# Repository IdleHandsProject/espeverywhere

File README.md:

# ESPEverywhere
ESP8266 Special Make/100 Kickstarter Edition

Check out why this board exists here:
https://www.youtube.com/watch?v=67Kh_ikb-ds

Thanks to the Backers of the #Make100(And the others as well!):  
Rolandas Launikonis  
Erlend Schei  
Andrew Chalkley  
Anthony Castaneda  
APSoft  
Arjuna Chatrathi  
Ashutosh Dubey  
Avinash Magdum  
BLUNT  
Bobby C C Wong  
Brian Linaburg  
Brian Willis  
Bruce Shipman  
Burrish  
DeltaLima  
Cardel Quaiatto  
Chaz Stone  
Chris Arnesen  
Christian Wilhelm  
Craig Hissett  
Dan Rothstein  
Danny Yo  
David Choi  
Death by snu snu  
Doug  
Fabio Cevasco  
Francisco Ribeiro  
Francesco Farruggia  
Grégoire Gustin  
Hank Terwilliger  
Hanya-zou  
Jeff Herndon  
Joe Key  
Jon Peer  
Jordan Moore  
Chris Cunningham  
Lewis Harrison-Wood  
Marco Hegenberg  
Mark Lee  
Mark Selph  
Milan Maletic  
Michael Gwincinski  
Mike Paulson  
Tim Lawson  
Michael Miranda  
Nick Piper  
Nick Goodall  
Nuno Santos  
PHK  
Wayne San  
Rob Arao  
Russell Calbert  
S. Lee Fowler  
Shabaz Mohammad  
SmilingRex Reyes  
Stephan Thomas  
Steve Farrage  
Will Ryan  
Yitzi Baum  

The ESP Everywhere was made to take part in the Kickstarter Make/100 Campaign
You can get 1 of 100 boards assembled by me. Or you can Make your own.
Kickstarter is here:
https://www.kickstarter.com/projects/idlehandsdev/esp-everywhere-kickstarter-special-make-100

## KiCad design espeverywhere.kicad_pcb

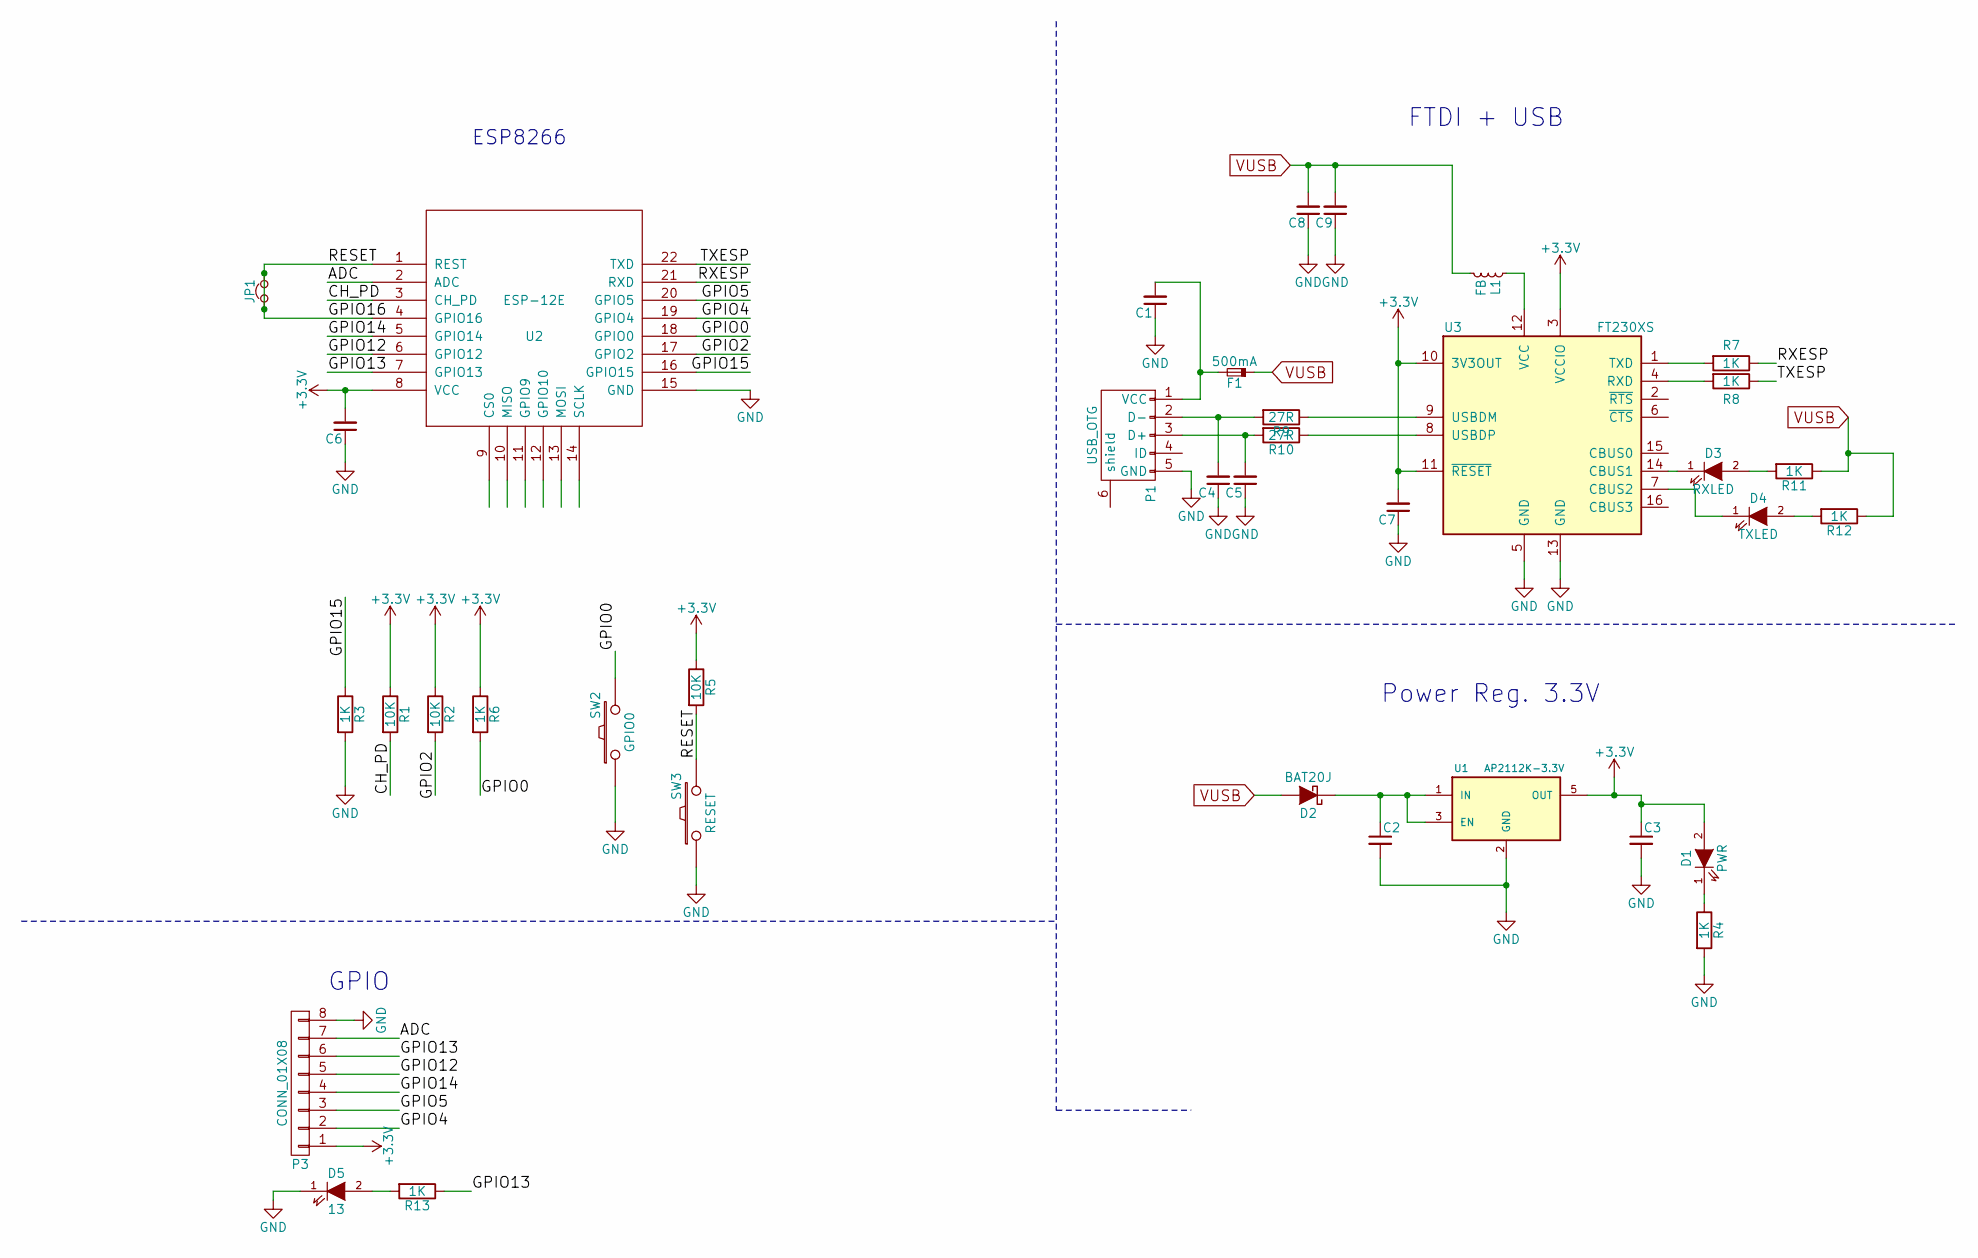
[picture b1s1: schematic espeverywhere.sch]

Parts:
C1, C7, C8: 0.1uF; C_0402_Hand; Digikey Part No. 490-6328-1-ND
C2: 1uF; C_0402_Hand; Digikey Part No. 490-1320-1-ND
C3: 2.2uF; C_0402_Hand; Digikey Part No. 490-10451-1-ND
C4, C5: 47pF; C_0402_Hand; Digikey Part No. 490-6241-1-ND
C6, C9: 10uF; C_0805; Digikey Part No. 490-1718-1-ND
D1: PWR; Led_0603; Digikey Part No. 160-1447-1-ND
D2: BAT20J; sod323; Digikey Part No. 497-3381-1-ND
D3: RXLED; Led_0603; Digikey Part No. 160-1448-1-ND
D4: TXLED; Led_0603; Digikey Part No. 160-1446-1-ND
D5: 13; Led_0603; Digikey Part No. 160-1446-1-ND
F1: 500mA; c_1206; Digikey Part No. 507-1802-1-ND
JP1: Jumper_NC_Small; SOLDER-JUMPER_1-WAY-CLOSED
L1: FB; R_0805_HandSoldering; Digikey Part No. 240-2390-1-ND
P1: USB_OTG; Digikey Part No. 609-4618-1-ND
P3: CONN_01X08; Connectors_JST_SM08B-SRSS-TB; Digikey Part No. 455-1808-1-ND
R1, R2, R5: 10K; R_0402_Hand; Digikey Part No. 311-10KJRCT-ND
R3, R4, R6, R7, R8, R11, R12, R13: 1K; R_0402_Hand; Digikey Part No. 311-1.0KJRCT-ND
R9, R10: 27R; R_0402_Hand; Digikey Part No. 311-27JRCT-ND
SW2: GPIO0; PTS-LFS; Digikey Part No. CKN9112CT-ND
SW3: RESET; PTS-LFS; Digikey Part No. CKN9112CT-ND
U1: AP2112K-3.3V; SOT-23-5; Digikey Part No. AP2112K-3.3TRG1DICT-ND
U2: ESP-12E
U3: FT230XS; SSOP-16_3.9x4.9mm_Pitch0.635mm; Digikey Part No. 768-1135-1-ND

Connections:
+3V3: C3.1, C6.2, C7.2, D1.2 (A), P3.1, R1.1, R2.1, R5.1, R6.1, U1.5 (OUT), U2.8 (VCC), U3.3 (VCCIO), U3.10 (3V3OUT), U3.11 (~RESET)
/ADC: P3.7, U2.2 (ADC)
/CH_PD: R1.2, U2.3 (CH_PD)
/GPIO0: R6.2, SW2.2, U2.18 (GPIO0)
/GPIO2: R2.2, U2.17 (GPIO2)
/GPIO4: P3.2, U2.19 (GPIO4)
/GPIO5: P3.3, U2.20 (GPIO5)
/GPIO12: P3.5, U2.6 (GPIO12)
/GPIO13: P3.6, R13.1, U2.7 (GPIO13)
/GPIO14: P3.4, U2.5 (GPIO14)
/GPIO15: R3.1, U2.16 (GPIO15)
/GPIO16: JP1.1, JP1.2, R5.2, SW3.2, U2.1 (REST), U2.4 (GPIO16)
/RXESP: R7.1, U2.21 (RXD)
/TXESP: R8.1, U2.22 (TXD)
GND: C1.1, C2.2, C3.2, C4.1, C5.1, C6.1, C7.1, C8.1, C9.1, D5.1 (K), P1.5 (GND), P3.8, R3.2, R4.2, SW2.1, SW3.1, U1.2 (GND), U2.15 (GND), U3.5 (GND), U3.13 (GND)
unnamed: C1.2, F1.2, P1.1 (VCC)
unnamed: C2.1, D2.1 (K), U1.1 (IN), U1.3 (EN)
unnamed: C4.2, P1.2 (D-), R9.2
unnamed: C5.2, P1.3 (D+), R10.2
unnamed: D1.1 (K), R4.1
unnamed: D3.1 (K), U3.14 (CBUS1)
unnamed: D3.2 (A), R11.2
unnamed: D4.1 (K), U3.7 (CBUS2)
unnamed: D4.2 (A), R12.2
unnamed: D5.2 (A), R13.2
unnamed: L1.1, U3.12 (VCC)
unnamed: R7.2, U3.1 (TXD)
unnamed: R8.2, U3.4 (RXD)
unnamed: R9.1, U3.9 (USBDM)
unnamed: R10.1, U3.8 (USBDP)
VUSB: C8.2, C9.2, D2.2 (A), F1.1, L1.2, R11.1, R12.1

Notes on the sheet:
ESP8266
FTDI + USB
GPIO
Power Reg. 3.3V

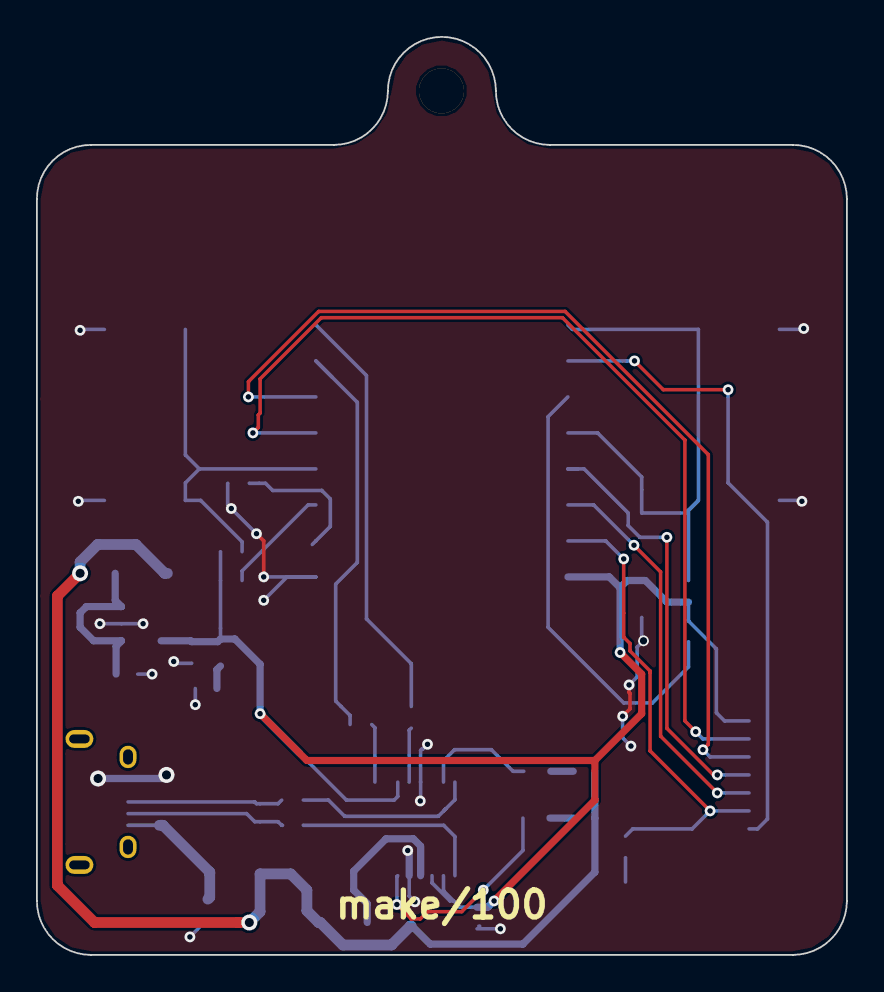
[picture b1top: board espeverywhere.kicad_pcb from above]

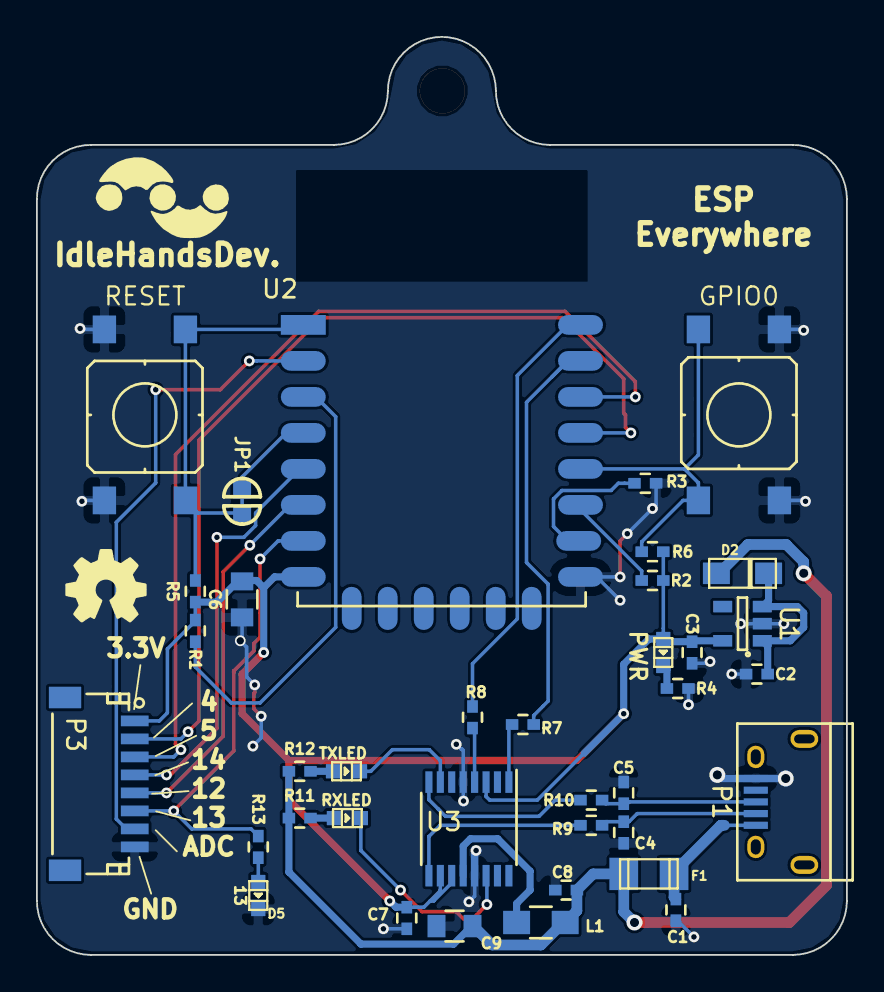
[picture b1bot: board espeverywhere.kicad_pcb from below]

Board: 2 copper layers, 45.0 x 51.0 mm, 37 parts (37 on the bottom side), 31 nets.

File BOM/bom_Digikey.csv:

ref,value,footprint,Digikey Part No.,Mouser Part No.,Quantity
C1 C7 C8,0.1uF,project_footprints:C_0402_Hand,490-6328-1-ND,,3
L1,FB,Resistors_SMD:R_0805_HandSoldering,240-2390-1-ND,,1
C4 C5,47pF,project_footprints:C_0402_Hand,490-6241-1-ND,,2
D2,BAT20J,project_footprints:sod323,497-3381-1-ND,,1
C2,1uF,project_footprints:C_0402_Hand,490-1320-1-ND,,1
D3,RXLED,idlehands_footprints:Led_0603,160-1448-1-ND,,1
U1,AP2112K-3.3V,TO_SOT_Packages_SMD:SOT-23-5,AP2112K-3.3TRG1DICT-ND,,1
D4 D5,TXLED,idlehands_footprints:Led_0603,160-1446-1-ND,,2
U3,FT230XS,Housings_SSOP:SSOP-16_3.9x4.9mm_Pitch0.635mm,768-1135-1-ND,,1
R9 R10,27R,idlehands_footprints:R_0402_Hand,311-27JRCT-ND,,2
F1,500mA,idlehands_footprints:c_1206,507-1802-1-ND,,1
P1,USB_OTG,,609-4618-1-ND,,1
D1,PWR,idlehands_footprints:Led_0603,160-1447-1-ND,,1
R1 R2 R5,10K,idlehands_footprints:R_0402_Hand,311-10KJRCT-ND,,3
R4 R3 R6 R7 R8 R11 R12 R13,1K,idlehands_footprints:R_0402_Hand,311-1.0KJRCT-ND,,8
C3,2.2uF,project_footprints:C_0402_Hand,490-10451-1-ND,,1
C6 C9,10uF,project_footprints:C_0402_Hand,490-1718-1-ND,,2

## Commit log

2017-01-30 Updated BOM and Gerbs
2017-02-01 Changed JST-SH-6 to 8 Pin
2017-02-01 Breakout Board added
2017-05-01 Added default testing firmware
